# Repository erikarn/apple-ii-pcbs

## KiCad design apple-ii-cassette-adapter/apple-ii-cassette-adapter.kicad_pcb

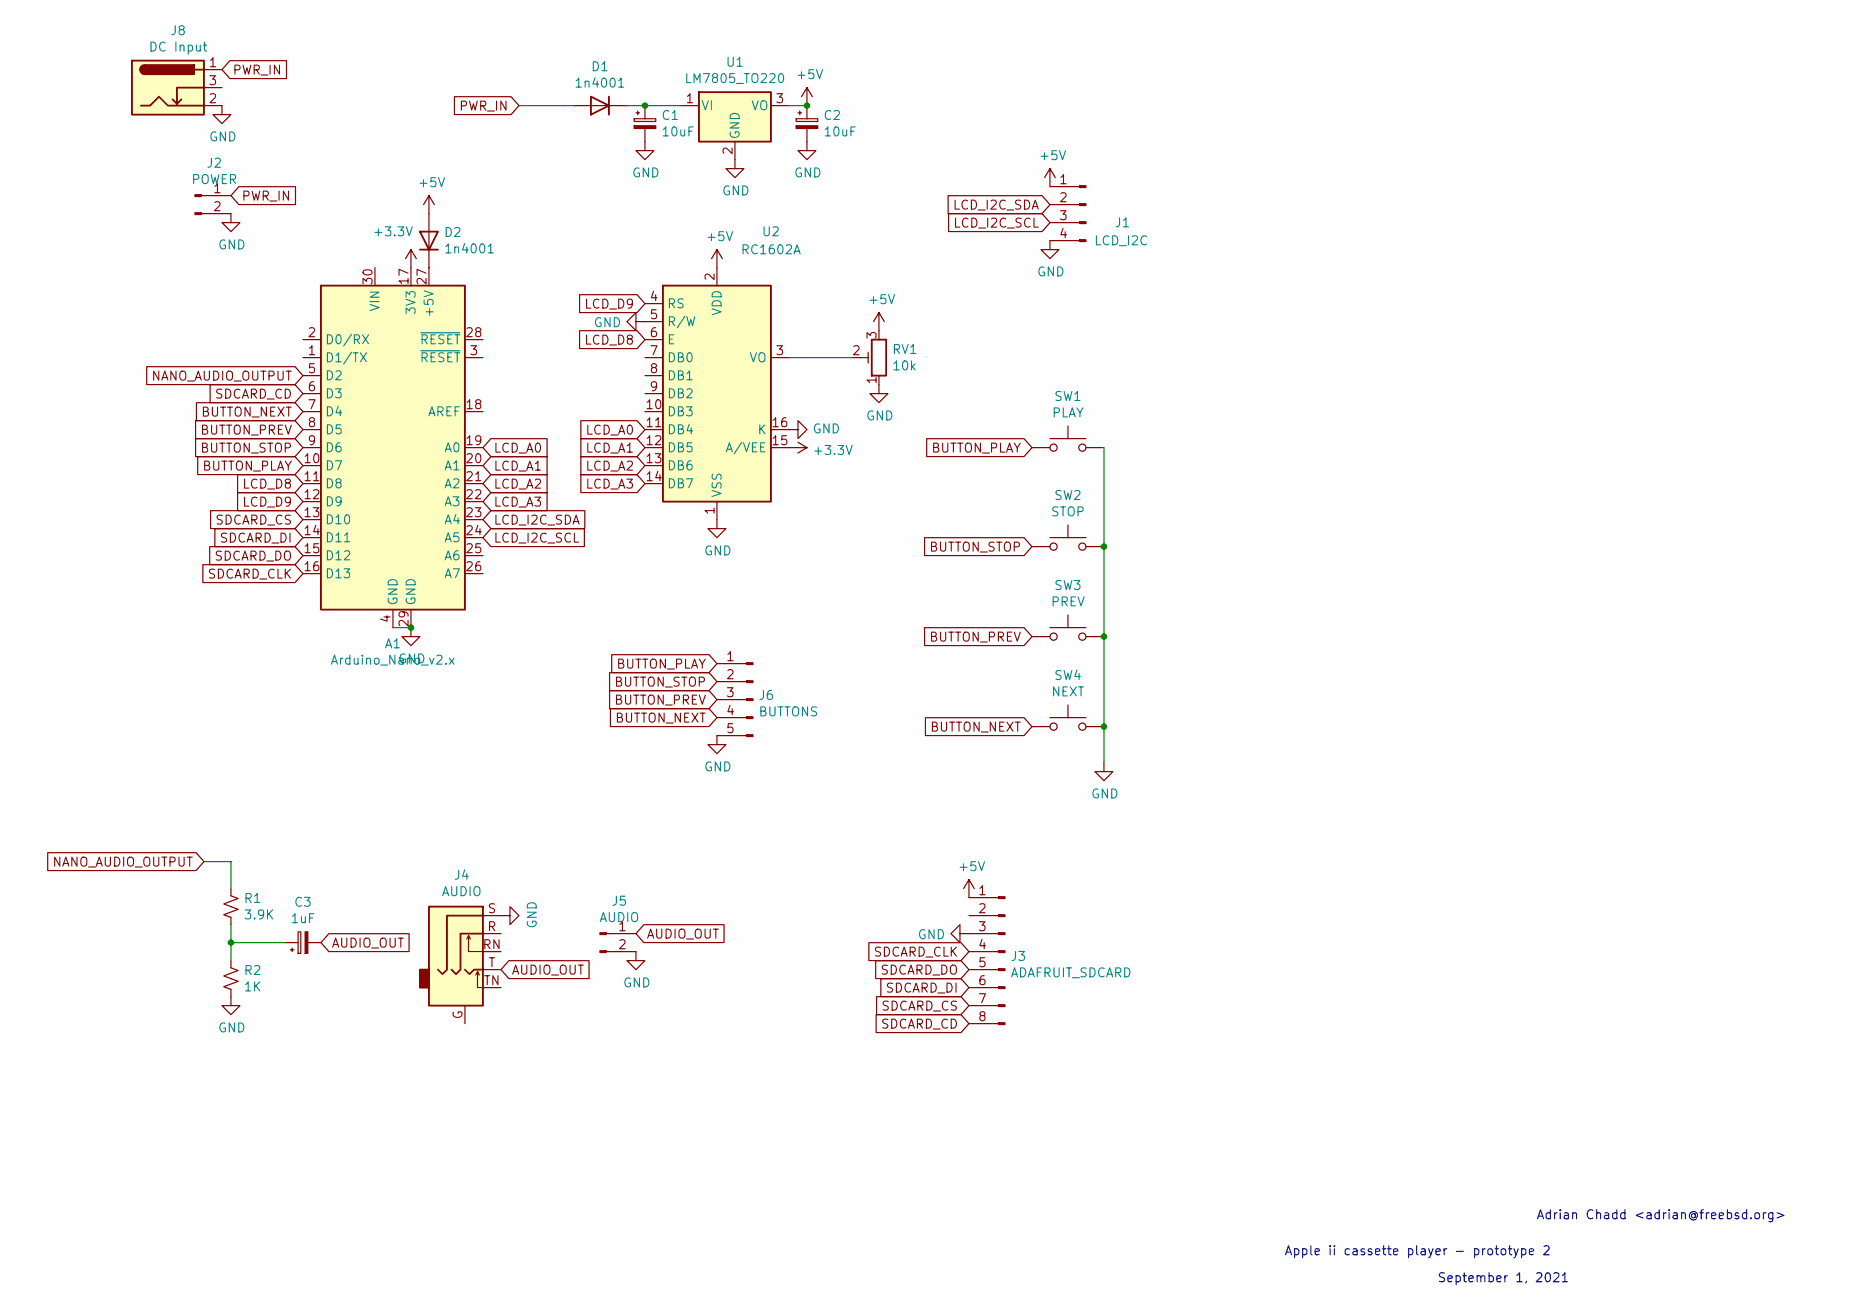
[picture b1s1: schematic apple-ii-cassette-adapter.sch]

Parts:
A1: Arduino_Nano_v2.x; Arduino_Nano
C1, C2: 10uF; CP_Radial_D6.3mm_P2.50mm
C3: 1uF; CP_Radial_D6.3mm_P2.50mm
D1, D2: 1n4001; D_DO-15_P10.16mm_Horizontal
J1: LCD_I2C; PinHeader_1x04_P2.54mm_Vertical
J2: POWER; PinHeader_1x02_P2.54mm_Vertical
J3: ADAFRUIT_SDCARD; PinHeader_1x08_P2.54mm_Vertical
J4: AUDIO; Jack_3.5mm_Ledino_KB3SPRS_Horizontal
J5: AUDIO; PinHeader_1x02_P2.54mm_Vertical
J6: BUTTONS; PinHeader_1x05_P2.54mm_Vertical
J8: DC Input; BarrelJack_CUI_PJ-102AH_Horizontal
R1: 3.9K; R_Axial_DIN0207_L6.3mm_D2.5mm_P2.54mm_Vertical
R2: 1K; R_Axial_DIN0207_L6.3mm_D2.5mm_P2.54mm_Vertical
RV1: 10k; Potentiometer_Bourns_3266P_Horizontal
SW1: PLAY; KSA_Tactile_SPST
SW2: STOP; KSA_Tactile_SPST
SW3: PREV; KSA_Tactile_SPST
SW4: NEXT; KSA_Tactile_SPST
U1: LM7805_TO220; TO-220-3_Vertical
U2: RC1602A

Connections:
+3V3: A1.17 (3V3), U2.15 (A/VEE)
+5V: C2.1, D2.2 (A), J1.1, J3.1, RV1.3, U1.3 (VO), U2.2 (VDD)
AUDIO_OUT: C3.2, J4.T, J5.1
BUTTON_NEXT: A1.7 (D4), J6.4, SW4.1
BUTTON_PLAY: A1.10 (D7), J6.1, SW1.1
BUTTON_PREV: A1.8 (D5), J6.3, SW3.1
BUTTON_STOP: A1.9 (D6), J6.2, SW2.1
GND: A1.4 (GND), A1.29 (GND), C1.2, C2.2, J1.4, J2.2, J3.3, J4.S, J5.2, J6.5, J8.2, R2.2, RV1.1, SW1.2, SW2.2, SW3.2, SW4.2, U1.2 (GND), U2.1 (VSS), U2.5 (R/W), U2.16 (K)
LCD_A0: A1.19 (A0), U2.11 (DB4)
LCD_A1: A1.20 (A1), U2.12 (DB5)
LCD_A2: A1.21 (A2), U2.13 (DB6)
LCD_A3: A1.22 (A3), U2.14 (DB7)
LCD_D8: A1.11 (D8), U2.6 (E)
LCD_D9: A1.12 (D9), U2.4 (RS)
LCD_I2C_SCL: A1.24 (A5), J1.3
LCD_I2C_SDA: A1.23 (A4), J1.2
NANO_AUDIO_OUTPUT: A1.5 (D2), R1.1
unnamed: A1.27 (+5V), D2.1 (K)
unnamed: C1.1, D1.1 (K), U1.1 (VI)
unnamed: C3.1, R1.2, R2.1
unnamed: RV1.2, U2.3 (VO)
PWR_IN: D1.2 (A), J2.1, J8.1
SDCARD_CD: A1.6 (D3), J3.8
SDCARD_CLK: A1.16 (D13), J3.4
SDCARD_CS: A1.13 (D10), J3.7
SDCARD_DI: A1.14 (D11), J3.6
SDCARD_DO: A1.15 (D12), J3.5

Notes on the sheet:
September 1, 2021
Adrian Chadd <adrian@freebsd.org>
Apple ii cassette player - prototype 2

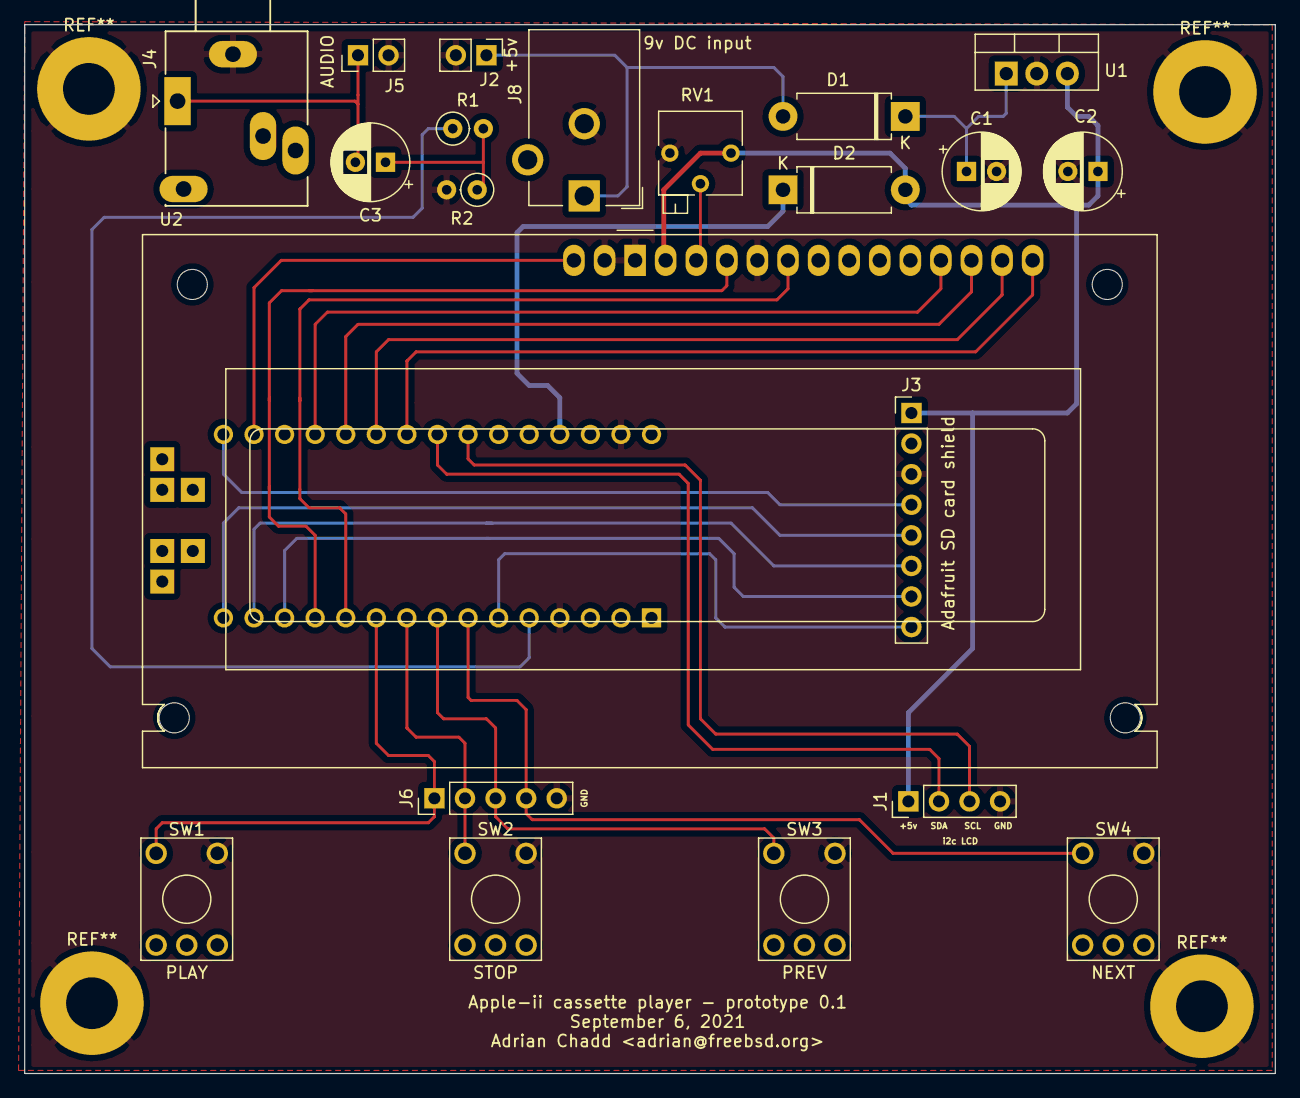
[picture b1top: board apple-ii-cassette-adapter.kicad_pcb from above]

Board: 2 copper layers, 103.9 x 87.1 mm, 22 parts (1 on the bottom side), 27 nets.

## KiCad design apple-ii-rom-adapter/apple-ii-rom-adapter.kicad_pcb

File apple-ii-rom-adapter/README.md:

# apple-II ROM adapter

This is a simple project to replace all the ROMS in an Apple-II with
a single EEPROM that holds enough to store both the applesoft and
integer BASIC ROM sets.

Yes, there are plenty of other solutions out there.  I built this
because I wanted to learn more about KiCAD and PCB layout.

## How it works

It's pretty simple, really:

 * It plugs into the D0 ROM and 74LS138 IC that does IO and ROM
   space decoding.
 * It uses an 28C256 32 kilobyte 8 bit parallel EEPROM for storage,
   which stores 2 x 12 kilobyte ROM images.
 * It uses a 74LS20 (dual 4-input NAND gate) and 74LS02 (NOR gate)
   to decode the 74LS138 output enable pins to enable the ROM.
 * And it correctly handles the inhibit line from the IO slots
   which is used by the language card to disable the on-board ROMs.

## Construction

It's a bit tricky to solder the header pins in.

 * Start by putting in the right hand side of pins in J3 that go into
   the apple-II socket - these are underneath the IC socket at U3.
 * Then solder in U3.
 * Then solder in the other row of pins for J3.

The pins at J2 are less problematic because there's more space; I'd solder
in the pins at J2 first, and then the socket U1.

The rest of it is straight forward.

## Flashing the ROM

The ROM is decoded in a pretty simple way - /CE is asserted for D000 -> F800.
But to simplify wiring, I ran the address lines out to the EEPROM.
So the first 2K in each half of the 16K image is unused, and should just
be kept blank.

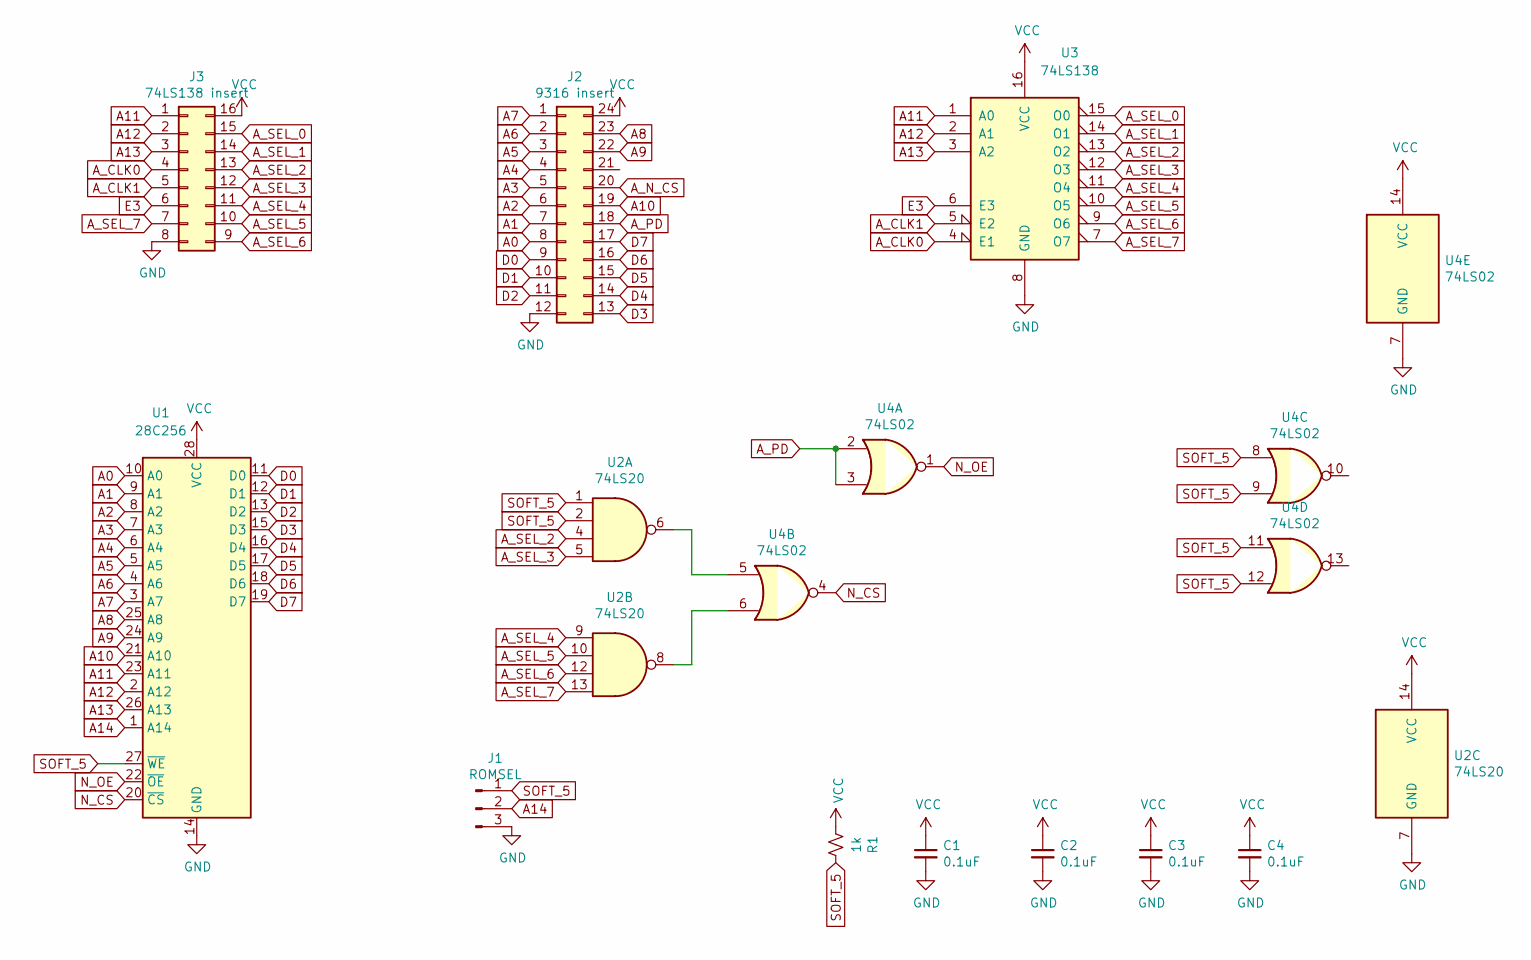
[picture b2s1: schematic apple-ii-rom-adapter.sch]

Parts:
C1, C2, C3, C4: 0.1uF; C_Disc_D5.0mm_W2.5mm_P5.00mm
J1: ROMSEL; PinHeader_1x03_P2.54mm_Vertical
J2: 9316 insert; DIP-24_W15.24mm_Socket
J3: 74LS138 insert; DIP-16_W7.62mm_Socket
R1: 1k; R_Axial_DIN0207_L6.3mm_D2.5mm_P7.62mm_Horizontal
U1: 28C256; DIP-28_W15.24mm_Socket
U2: 74LS20; DIP-14_W7.62mm_Socket
U3: 74LS138; DIP-16_W7.62mm_Socket
U4: 74LS02; DIP-14_W7.62mm_Socket

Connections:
A0: J2.8, U1.10 (A0)
A1: J2.7, U1.9 (A1)
A2: J2.6, U1.8 (A2)
A3: J2.5, U1.7 (A3)
A4: J2.4, U1.6 (A4)
A5: J2.3, U1.5 (A5)
A6: J2.2, U1.4 (A6)
A7: J2.1, U1.3 (A7)
A8: J2.23, U1.25 (A8)
A9: J2.22, U1.24 (A9)
A10: J2.19, U1.21 (A10)
A11: J3.1, U1.23 (A11), U3.1 (A0)
A12: J3.2, U1.2 (A12), U3.2 (A1)
A13: J3.3, U1.26 (A13), U3.3 (A2)
A14: J1.2, U1.1 (A14)
A_CLK0: J3.4, U3.4 (E1)
A_CLK1: J3.5, U3.5 (E2)
A_N_CS: J2.20
A_PD: J2.18, U4.2, U4.3
A_SEL_0: J3.15, U3.15 (O0)
A_SEL_1: J3.14, U3.14 (O1)
A_SEL_2: J3.13, U2.4, U3.13 (O2)
A_SEL_3: J3.12, U2.5, U3.12 (O3)
A_SEL_4: J3.11, U2.9, U3.11 (O4)
A_SEL_5: J3.10, U2.10, U3.10 (O5)
A_SEL_6: J3.9, U2.12, U3.9 (O6)
A_SEL_7: J3.7, U2.13, U3.7 (O7)
D0: J2.9, U1.11 (D0)
D1: J2.10, U1.12 (D1)
D2: J2.11, U1.13 (D2)
D3: J2.13, U1.15 (D3)
D4: J2.14, U1.16 (D4)
D5: J2.15, U1.17 (D5)
D6: J2.16, U1.18 (D6)
D7: J2.17, U1.19 (D7)
E3: J3.6, U3.6 (E3)
GND: C1.2, C2.2, C3.2, C4.2, J1.3, J2.12, J3.8, U1.14 (GND), U2.7 (GND), U3.8 (GND), U4.7 (GND)
N_CS: U1.20 (~CS), U4.4
N_OE: U1.22 (~OE), U4.1
unnamed: U2.6, U4.5
unnamed: U2.8, U4.6
SOFT_5: J1.1, R1.1, U1.27 (~WE), U2.1, U2.2, U4.8, U4.9, U4.11, U4.12
VCC: C1.1, C2.1, C3.1, C4.1, J2.24, J3.16, R1.2, U1.28 (VCC), U2.14 (VCC), U3.16 (VCC), U4.14 (VCC)

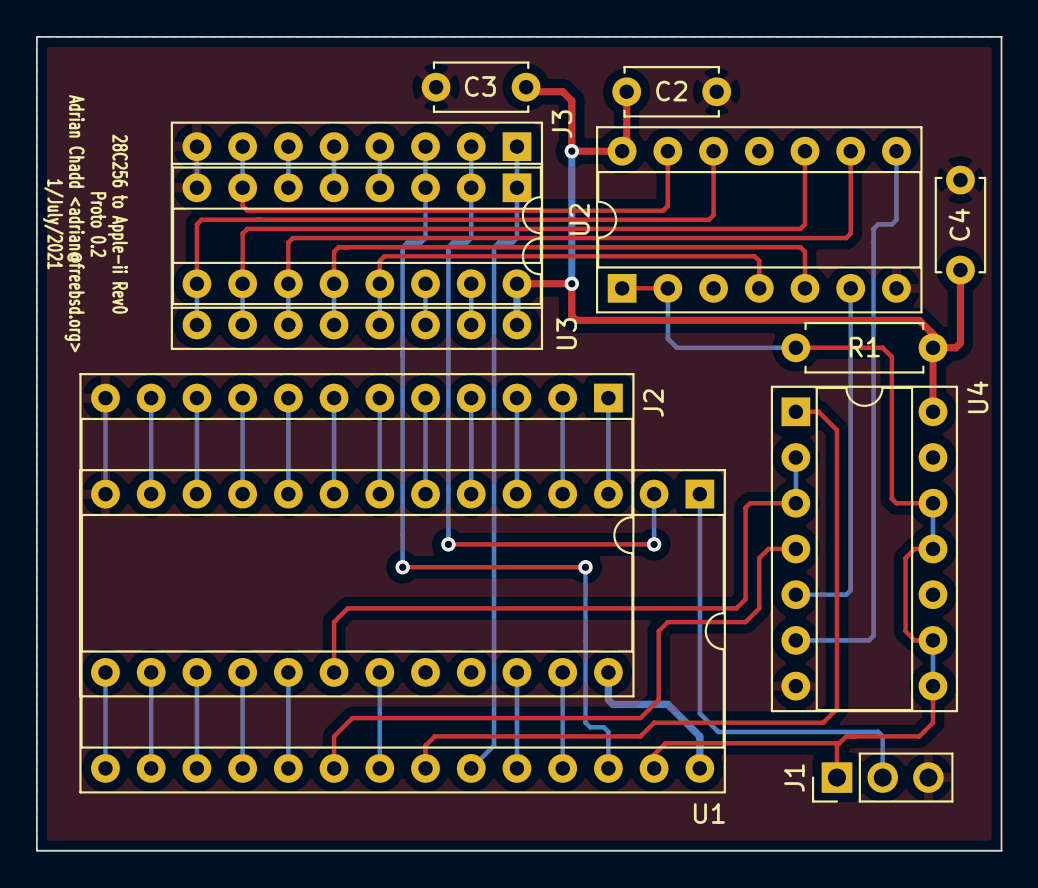
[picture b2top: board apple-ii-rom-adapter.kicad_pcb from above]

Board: 2 copper layers, 53.6 x 45.2 mm, 11 parts (0 on the bottom side), 42 nets.

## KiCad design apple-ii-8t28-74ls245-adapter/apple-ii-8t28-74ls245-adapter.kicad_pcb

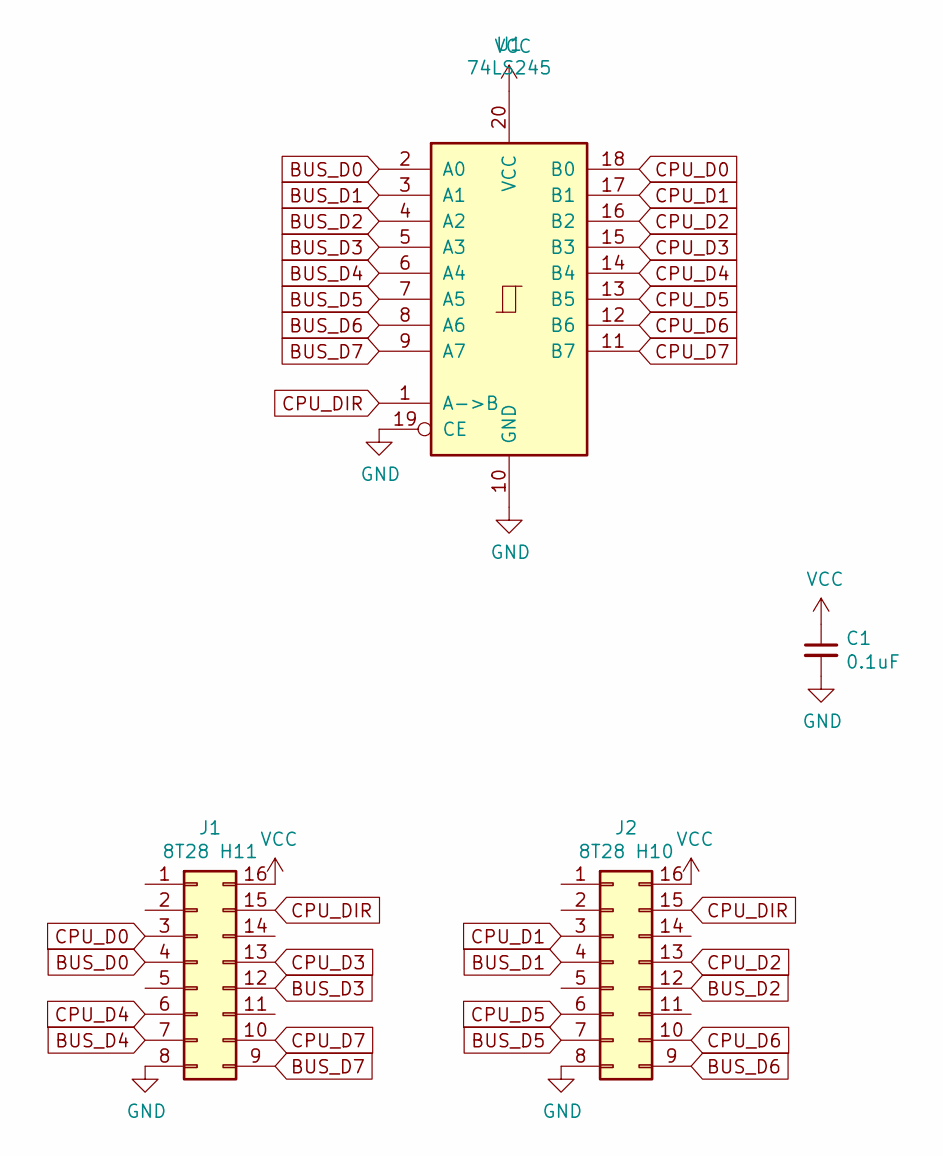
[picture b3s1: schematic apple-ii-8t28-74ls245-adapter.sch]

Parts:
C1: 0.1uF; C_Axial_L3.8mm_D2.6mm_P7.50mm_Horizontal
J1: 8T28 H11; DIP-16_W7.62mm_Socket
J2: 8T28 H10; DIP-16_W7.62mm_Socket
U1: 74LS245; DIP-20_W7.62mm_Socket

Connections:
BUS_D0: J1.4, U1.2 (A0)
BUS_D1: J2.4, U1.3 (A1)
BUS_D2: J2.12, U1.4 (A2)
BUS_D3: J1.12, U1.5 (A3)
BUS_D4: J1.7, U1.6 (A4)
BUS_D5: J2.7, U1.7 (A5)
BUS_D6: J2.9, U1.8 (A6)
BUS_D7: J1.9, U1.9 (A7)
CPU_D0: J1.3, U1.18 (B0)
CPU_D1: J2.3, U1.17 (B1)
CPU_D2: J2.13, U1.16 (B2)
CPU_D3: J1.13, U1.15 (B3)
CPU_D4: J1.6, U1.14 (B4)
CPU_D5: J2.6, U1.13 (B5)
CPU_D6: J2.10, U1.12 (B6)
CPU_D7: J1.10, U1.11 (B7)
CPU_DIR: J1.15, J2.15, U1.1 (A->B)
GND: C1.2, J1.8, J2.8, U1.10 (GND), U1.19 (CE)
VCC: C1.1, J1.16, J2.16, U1.20 (VCC)

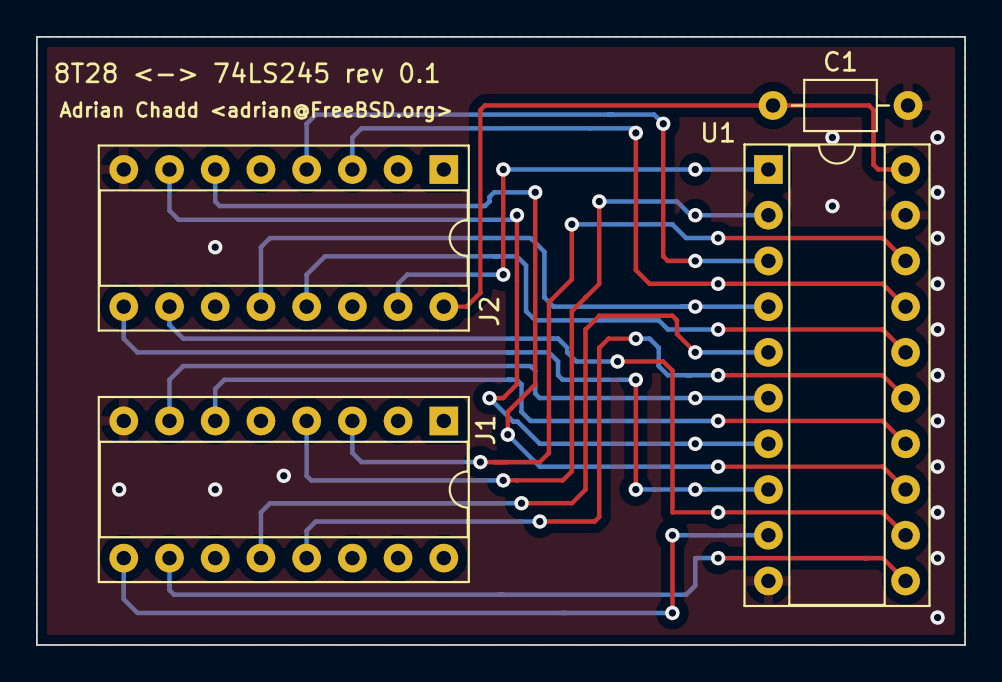
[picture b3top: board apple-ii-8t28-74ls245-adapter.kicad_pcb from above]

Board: 2 copper layers, 51.6 x 33.8 mm, 4 parts (0 on the bottom side), 19 nets.

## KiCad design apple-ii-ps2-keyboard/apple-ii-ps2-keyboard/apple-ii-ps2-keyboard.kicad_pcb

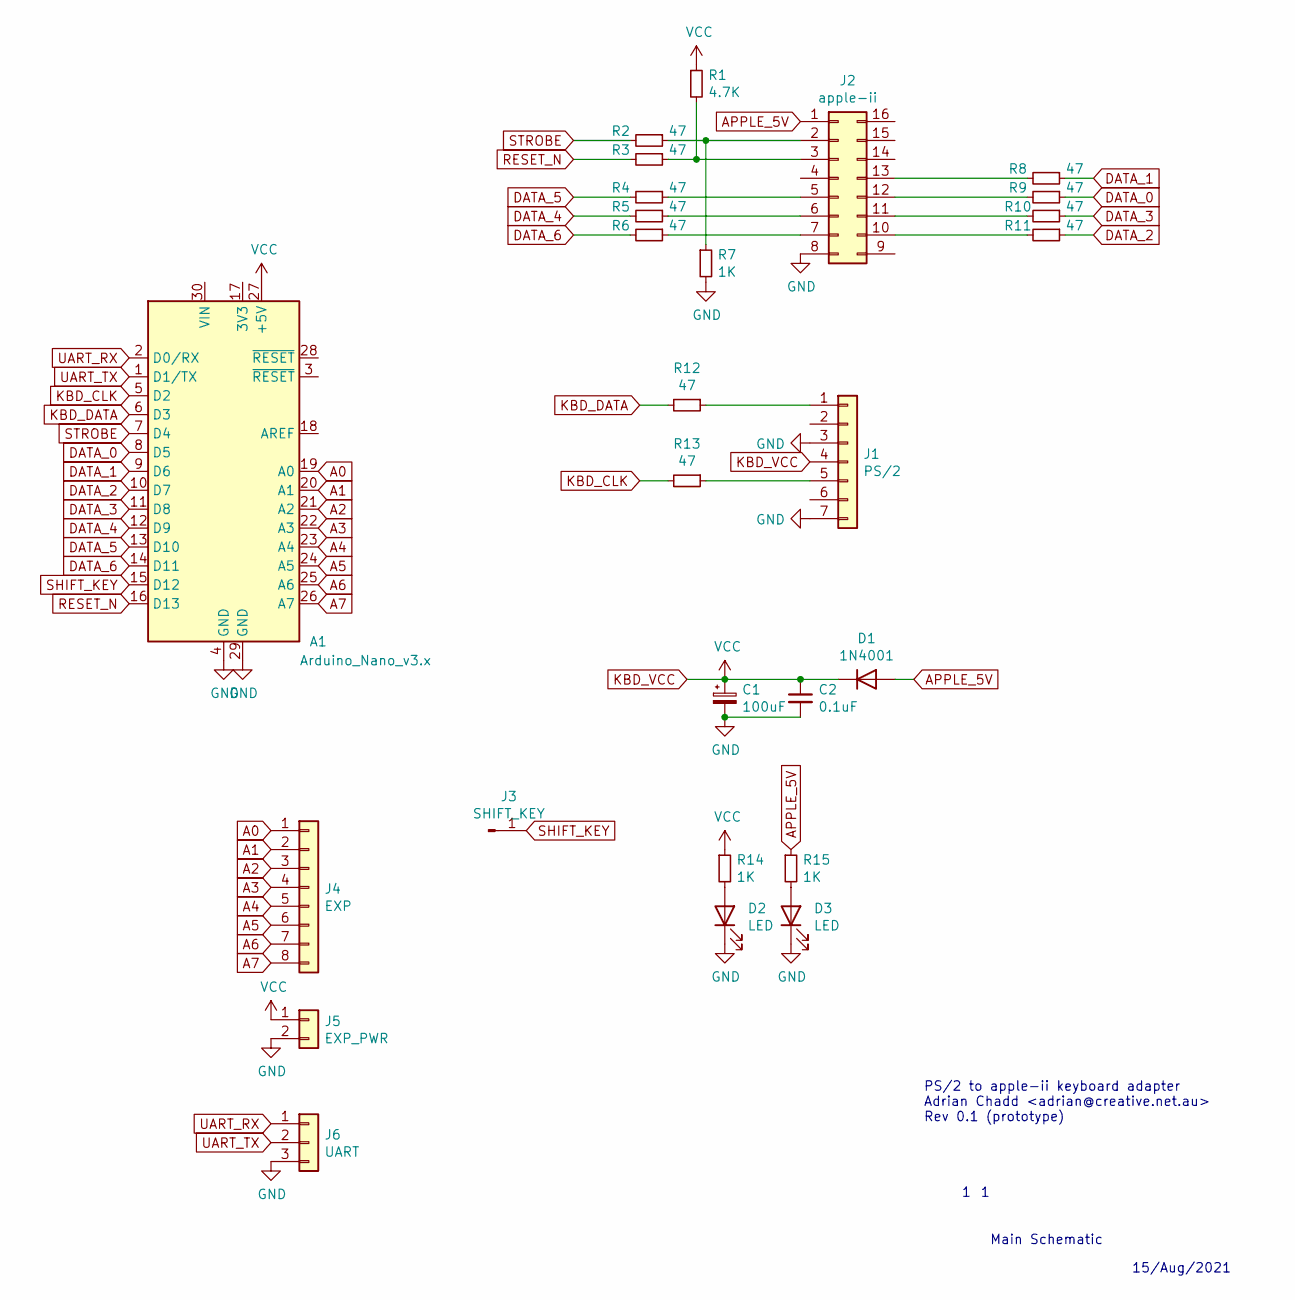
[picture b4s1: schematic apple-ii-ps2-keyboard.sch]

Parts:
A1: Arduino_Nano_v3.x; Arduino_Nano
C1: 100uF; CP_Radial_D5.0mm_P2.50mm
C2: 0.1uF; C_Disc_D3.8mm_W2.6mm_P2.50mm
D1: 1N4001; D_DO-41_SOD81_P10.16mm_Horizontal
D2, D3: LED; LED_D3.0mm
J1: PS/2; PinHeader_1x07_P2.54mm_Vertical
J2: apple-ii; DIP-16_W7.62mm_LongPads
J3: SHIFT_KEY; PinHeader_1x01_P2.54mm_Vertical
J4: EXP; PinHeader_1x08_P2.54mm_Vertical
J5: EXP_PWR; PinHeader_1x02_P2.54mm_Vertical
J6: UART; PinHeader_1x03_P2.54mm_Vertical
R1: 4.7K; R_Axial_DIN0204_L3.6mm_D1.6mm_P5.08mm_Horizontal
R2, R3, R4, R5, R6, R8, R9, R10, R11, R12, R13: 47; R_Axial_DIN0204_L3.6mm_D1.6mm_P5.08mm_Horizontal
R7, R14, R15: 1K; R_Axial_DIN0204_L3.6mm_D1.6mm_P5.08mm_Horizontal

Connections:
A0: A1.19 (A0), J4.1
A1: A1.20 (A1), J4.2
A2: A1.21 (A2), J4.3
A3: A1.22 (A3), J4.4
A4: A1.23 (A4), J4.5
A5: A1.24 (A5), J4.6
A6: A1.25 (A6), J4.7
A7: A1.26 (A7), J4.8
APPLE_5V: D1.2 (A), J2.1, R15.1
DATA_0: A1.8 (D5), R9.1
DATA_1: A1.9 (D6), R8.1
DATA_2: A1.10 (D7), R11.1
DATA_3: A1.11 (D8), R10.1
DATA_4: A1.12 (D9), R5.2
DATA_5: A1.13 (D10), R4.2
DATA_6: A1.14 (D11), R6.2
GND: A1.4 (GND), A1.29 (GND), C1.2, C2.2, D2.1 (K), D3.1 (K), J1.3, J1.7, J2.8, J5.2, J6.3, R7.2
KBD_CLK: A1.5 (D2), R13.2
KBD_DATA: A1.6 (D3), R12.2
KBD_VCC: A1.27 (+5V), C1.1, C2.1, D1.1 (K), J1.4, J5.1, R1.1, R14.1
unnamed: D2.2 (A), R14.2
unnamed: D3.2 (A), R15.2
unnamed: J1.1, R12.1
unnamed: J1.5, R13.1
unnamed: J2.2, R2.1, R7.1
unnamed: J2.3, R1.2, R3.1
unnamed: J2.5, R4.1
unnamed: J2.6, R5.1
unnamed: J2.7, R6.1
unnamed: J2.10, R11.2
unnamed: J2.11, R10.2
unnamed: J2.12, R9.2
unnamed: J2.13, R8.2
RESET_N: A1.16 (D13), R3.2
SHIFT_KEY: A1.15 (D12), J3.1
STROBE: A1.7 (D4), R2.2
UART_RX: A1.2 (D0/RX), J6.1
UART_TX: A1.1 (D1/TX), J6.2

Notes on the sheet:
Main Schematic
15/Aug/2021
PS/2 to apple-ii keyboard adapter Adrian Chadd <adrian@creative.net.au> Rev 0.1 (prototype)

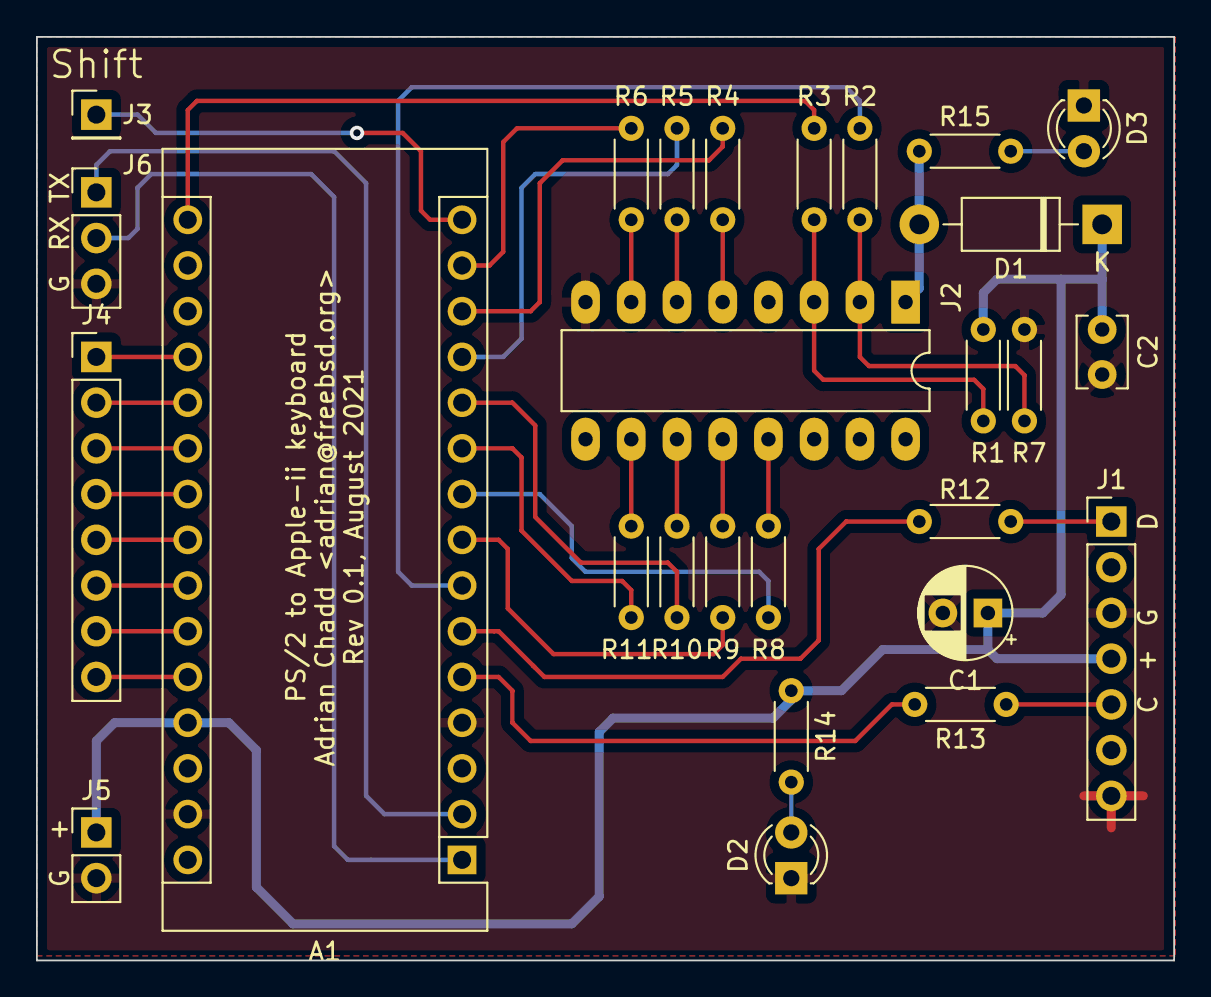
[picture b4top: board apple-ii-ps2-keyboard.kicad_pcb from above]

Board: 2 copper layers, 63.2 x 51.3 mm, 27 parts (0 on the bottom side), 38 nets.

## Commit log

2021-08-16 Initial library - but I think the nano is now included in kicad
2021-08-16 initial schematic for the apple-ii ps/2 adapter
2021-08-16 Add initial prototype PCB routing
    I'll look at this tomorrow before I send it out for printing.
2021-08-16 Update the description to say prototype
2021-08-16 * add shift button IO control for later * add the A0-A7 and power pins as expansion headers if I want to do anything else
2021-08-16 * add uart connector * add pin 7 on the ps/2 connector as a ground, for shield
    ok, this may be the thing I ship!
2021-08-17 .. not sure why this happened but ok?
2021-08-21 Copy over my apple ii pcbs
2021-08-21 add a basic readme
2021-08-23 add initial 65c02 / 8t28 symbols
2021-08-23 Start a rev7 schematic.
    This is the CPU page.
2021-08-30 Initial draft of the cassette adapter project!
    This pinout is a LITTLE different to what I prototyped, notably the buttons
    moved down a bit so D2 can be used as an interrupt.
2021-09-01 Add initial prototype schematic pdf
2021-09-01 Update title!
2021-09-03 Update schematic to aid in layout, start layout
2021-09-06 In progress schematic layout
    For some reason I don't have a ground pin on this audio jack footprint; i need
    to figure THAT out soon.
2021-09-07 Update schematic/PCB; this may actually work.
    "S" is the shield; not GND. Weird. Anyway, that's GND now.
2021-09-07 Route the audio path over buttons, /not/ over the SD card IO bus.
    This also saves a via.
2021-09-30 Update routing and schematic for the RC1602A LCD variant.
    It's not the adafruit one, and honestly I'm suprised kicad doesn't come with
    the adafruit part footprints, but baby steps.
2021-12-01 add the adafruit 16x2 rgb backlight LCD
